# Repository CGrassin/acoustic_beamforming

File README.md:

# Acoustic Beamforming experiments

This repository contains all the ressources for my acoustic beamforming experiment using Arduino. This original article is here: http://charleslabs.fr/en/project-Acoustic+beamsteering+with+a+speaker+array

Various pieces of code/ressource are sorted by folder.

## Code_Pattern

This folder contains code to compute beamforming patterns.

The main script is beamforming_pattern_gen.py. Usage: `python3 beamforming_pattern_gen.py -h` (shows the help and options)

Sample output (`python3 beamforming_pattern_gen.py -f 1000 -a 10`):

Also included is a geogebra file for uniform amplitude law pattern simulation.

## Code_Arduino

This folder contains the code generator and the libraries to program the Arduino. It computes the timing to get the proper frequncy and phase between the elements. Usage:

```sh
python3 beamforming_code_gen.py -f 1000 -a 10
```

Output: Arduino code for the generation of a 1000Hz frequency wave, steered to +10 degrees.

Note: there is also a fully working, but deprecated Java version of this script that I created prior to the python version.

## Electronics

This folder contains the 12 channels signal generator PCB based around the FM62429 chips and the Arduino Nano microcontroller board. I used the open-source EDA KiCad.

## Experiments_Data

*WORK IN PROGRESS* This folder contains the data collected for each measurement, in CSV format. The first line of each CSV file contains all information to figure out it content.

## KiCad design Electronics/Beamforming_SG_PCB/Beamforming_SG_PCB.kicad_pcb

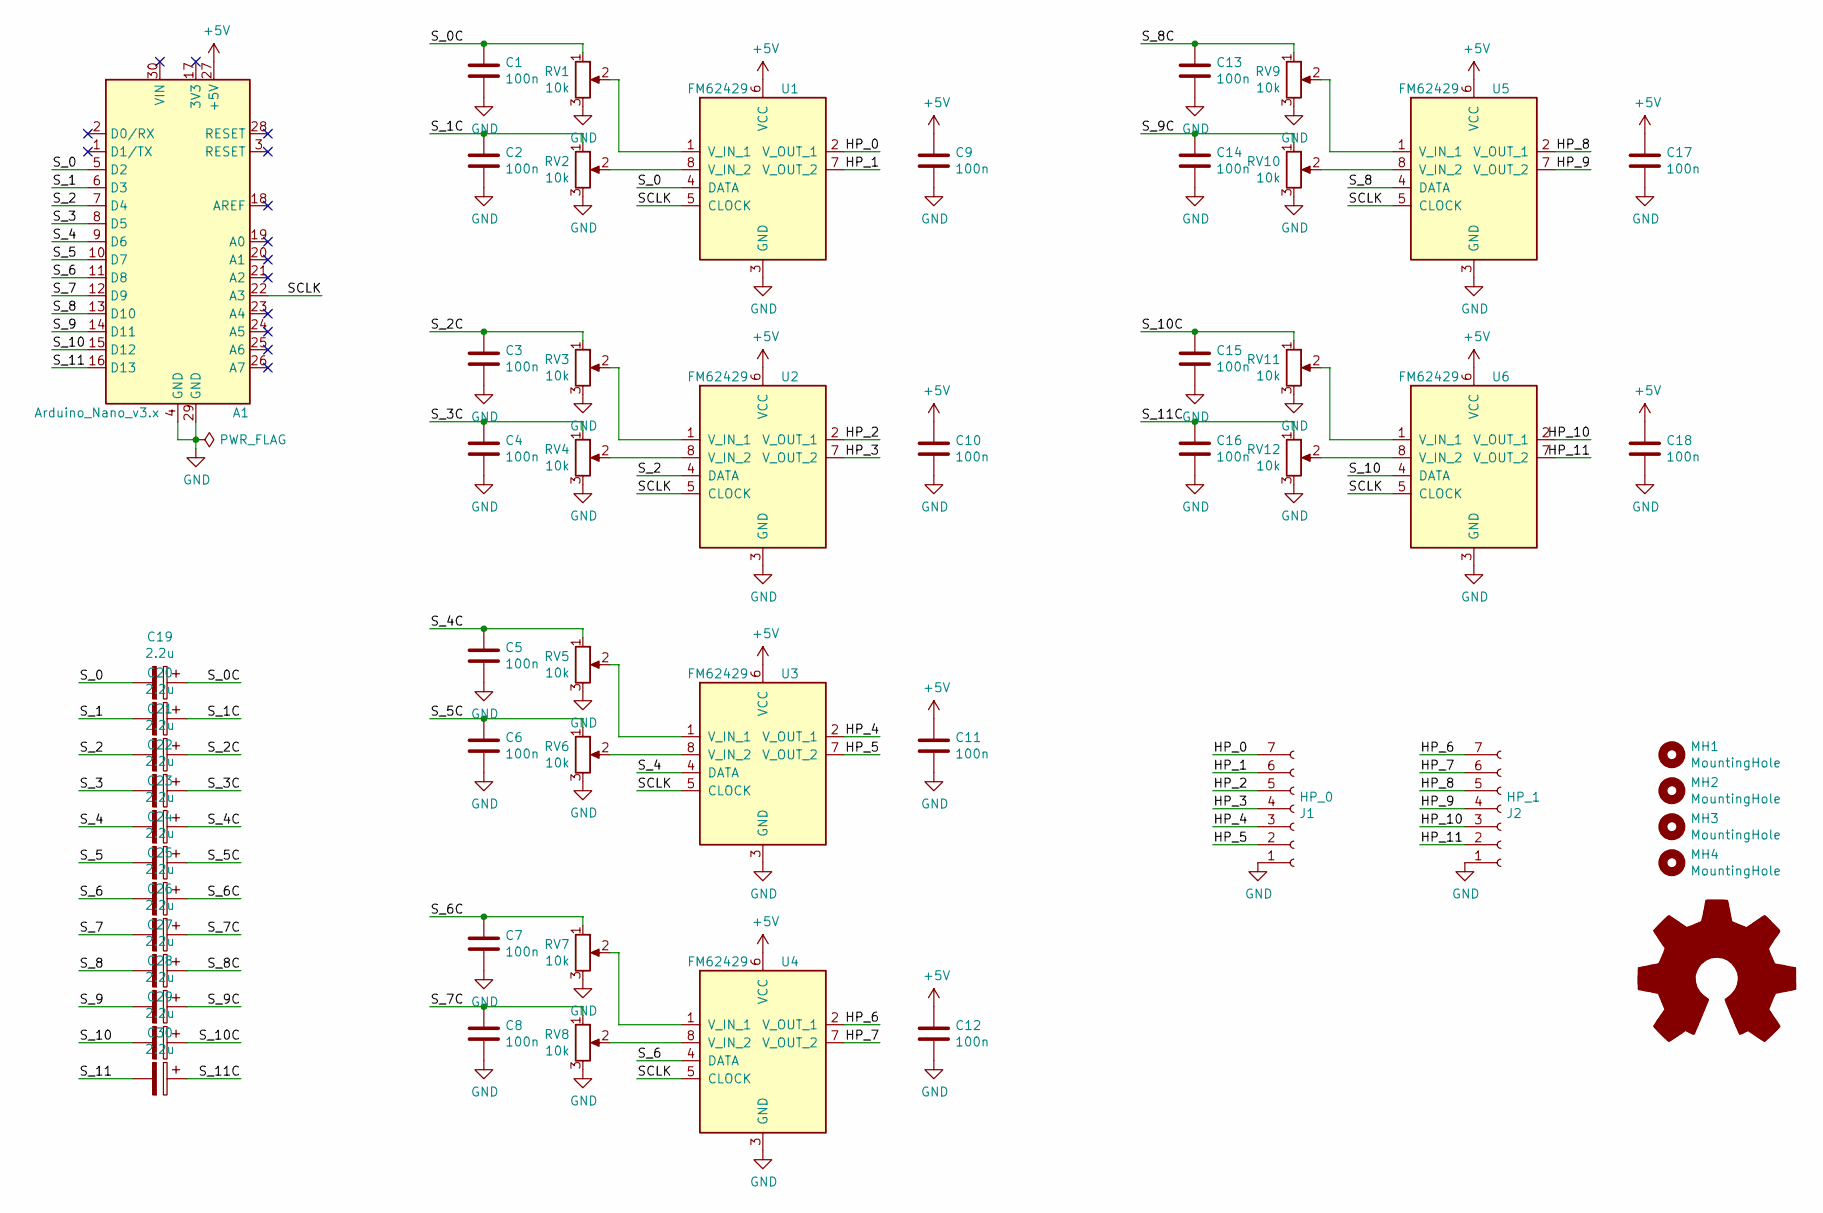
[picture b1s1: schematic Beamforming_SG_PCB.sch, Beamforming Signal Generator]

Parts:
A1: Arduino_Nano_v3.x; Arduino_Nano
C1, C2, C3, C4, C5, C6, C7, C8, C13, C14, C15, C16: 100n; C_0805_2012Metric
C9, C10, C11, C12, C17, C18: 100n; C_Disc_D4.3mm_W1.9mm_P5.00mm
C19, C20, C21, C22, C23, C24, C25, C26, C27, C28, C29, C30: 2.2u; C_0805_2012Metric
J1: HP_0; PinSocket_1x07_P2.54mm_Vertical
J2: HP_1; PinSocket_1x07_P2.54mm_Vertical
LOGO1: Logo_Open_Hardware_Large; OSHW-Symbol_8.9x8mm_SilkScreen
MH1, MH2, MH3, MH4: MountingHole; MountingHole_3.2mm_M3
RV1, RV2, RV3, RV4, RV5, RV6, RV7, RV8, RV9, RV10, RV11, RV12: 10k; Potentiometer_Bourns_3296W_Vertical
U1, U2, U3, U4, U5, U6: FM62429; DIP-8_W7.62mm

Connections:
+5V: A1.27 (+5V), C9.1, C10.1, C11.1, C12.1, C17.1, C18.1, U1.6 (VCC), U2.6 (VCC), U3.6 (VCC), U4.6 (VCC), U5.6 (VCC), U6.6 (VCC)
/HP_0: J1.7, U1.2 (V_OUT_1)
/HP_1: J1.6, U1.7 (V_OUT_2)
/HP_2: J1.5, U2.2 (V_OUT_1)
/HP_3: J1.4, U2.7 (V_OUT_2)
/HP_4: J1.3, U3.2 (V_OUT_1)
/HP_5: J1.2, U3.7 (V_OUT_2)
/HP_6: J2.7, U4.2 (V_OUT_1)
/HP_7: J2.6, U4.7 (V_OUT_2)
/HP_8: J2.5, U5.2 (V_OUT_1)
/HP_9: J2.4, U5.7 (V_OUT_2)
/HP_10: J2.3, U6.2 (V_OUT_1)
/HP_11: J2.2, U6.7 (V_OUT_2)
/SCLK: A1.22 (A3), U1.5 (CLOCK), U2.5 (CLOCK), U3.5 (CLOCK), U4.5 (CLOCK), U5.5 (CLOCK), U6.5 (CLOCK)
/S_0: A1.5 (D2), C19.2, U1.4 (DATA)
/S_0C: C1.1, C19.1, RV1.1
/S_1: A1.6 (D3), C20.2
/S_1C: C2.1, C20.1, RV2.1
/S_2: A1.7 (D4), C21.2, U2.4 (DATA)
/S_2C: C3.1, C21.1, RV3.1
/S_3: A1.8 (D5), C22.2
/S_3C: C4.1, C22.1, RV4.1
/S_4: A1.9 (D6), C23.2, U3.4 (DATA)
/S_4C: C5.1, C23.1, RV5.1
/S_5: A1.10 (D7), C24.2
/S_5C: C6.1, C24.1, RV6.1
/S_6: A1.11 (D8), C25.2, U4.4 (DATA)
/S_6C: C7.1, C25.1, RV7.1
/S_7: A1.12 (D9), C26.2
/S_7C: C8.1, C26.1, RV8.1
/S_8: A1.13 (D10), C27.2, U5.4 (DATA)
/S_8C: C13.1, C27.1, RV9.1
/S_9: A1.14 (D11), C28.2
/S_9C: C14.1, C28.1, RV10.1
/S_10: A1.15 (D12), C29.2, U6.4 (DATA)
/S_10C: C15.1, C29.1, RV11.1
/S_11: A1.16 (D13), C30.2
/S_11C: C16.1, C30.1, RV12.1
GND: A1.4 (GND), A1.29 (GND), C1.2, C2.2, C3.2, C4.2, C5.2, C6.2, C7.2, C8.2, C9.2, C10.2, C11.2, C12.2, C13.2, C14.2, C15.2, C16.2, C17.2, C18.2, J1.1, J2.1, RV1.3, RV2.3, RV3.3, RV4.3, RV5.3, RV6.3, RV7.3, RV8.3, RV9.3, RV10.3, RV11.3, RV12.3, U1.3 (GND), U2.3 (GND), U3.3 (GND), U4.3 (GND), U5.3 (GND), U6.3 (GND)
unnamed: RV1.2, U1.1 (V_IN_1)
unnamed: RV2.2, U1.8 (V_IN_2)
unnamed: RV3.2, U2.1 (V_IN_1)
unnamed: RV4.2, U2.8 (V_IN_2)
unnamed: RV5.2, U3.1 (V_IN_1)
unnamed: RV6.2, U3.8 (V_IN_2)
unnamed: RV7.2, U4.1 (V_IN_1)
unnamed: RV8.2, U4.8 (V_IN_2)
unnamed: RV9.2, U5.1 (V_IN_1)
unnamed: RV10.2, U5.8 (V_IN_2)
unnamed: RV11.2, U6.1 (V_IN_1)
unnamed: RV12.2, U6.8 (V_IN_2)

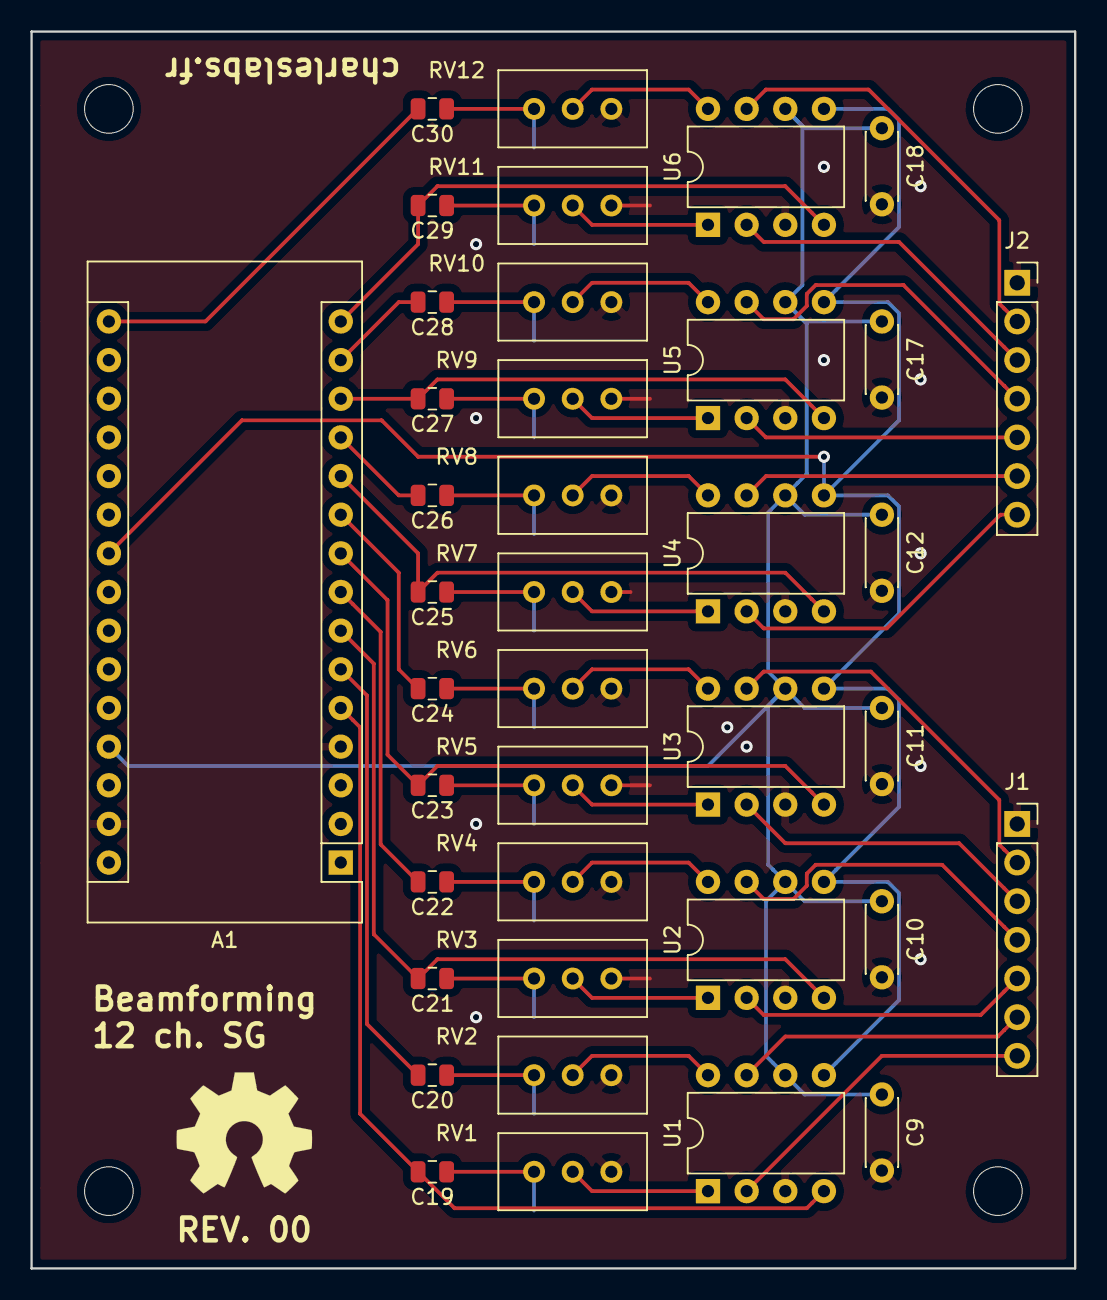
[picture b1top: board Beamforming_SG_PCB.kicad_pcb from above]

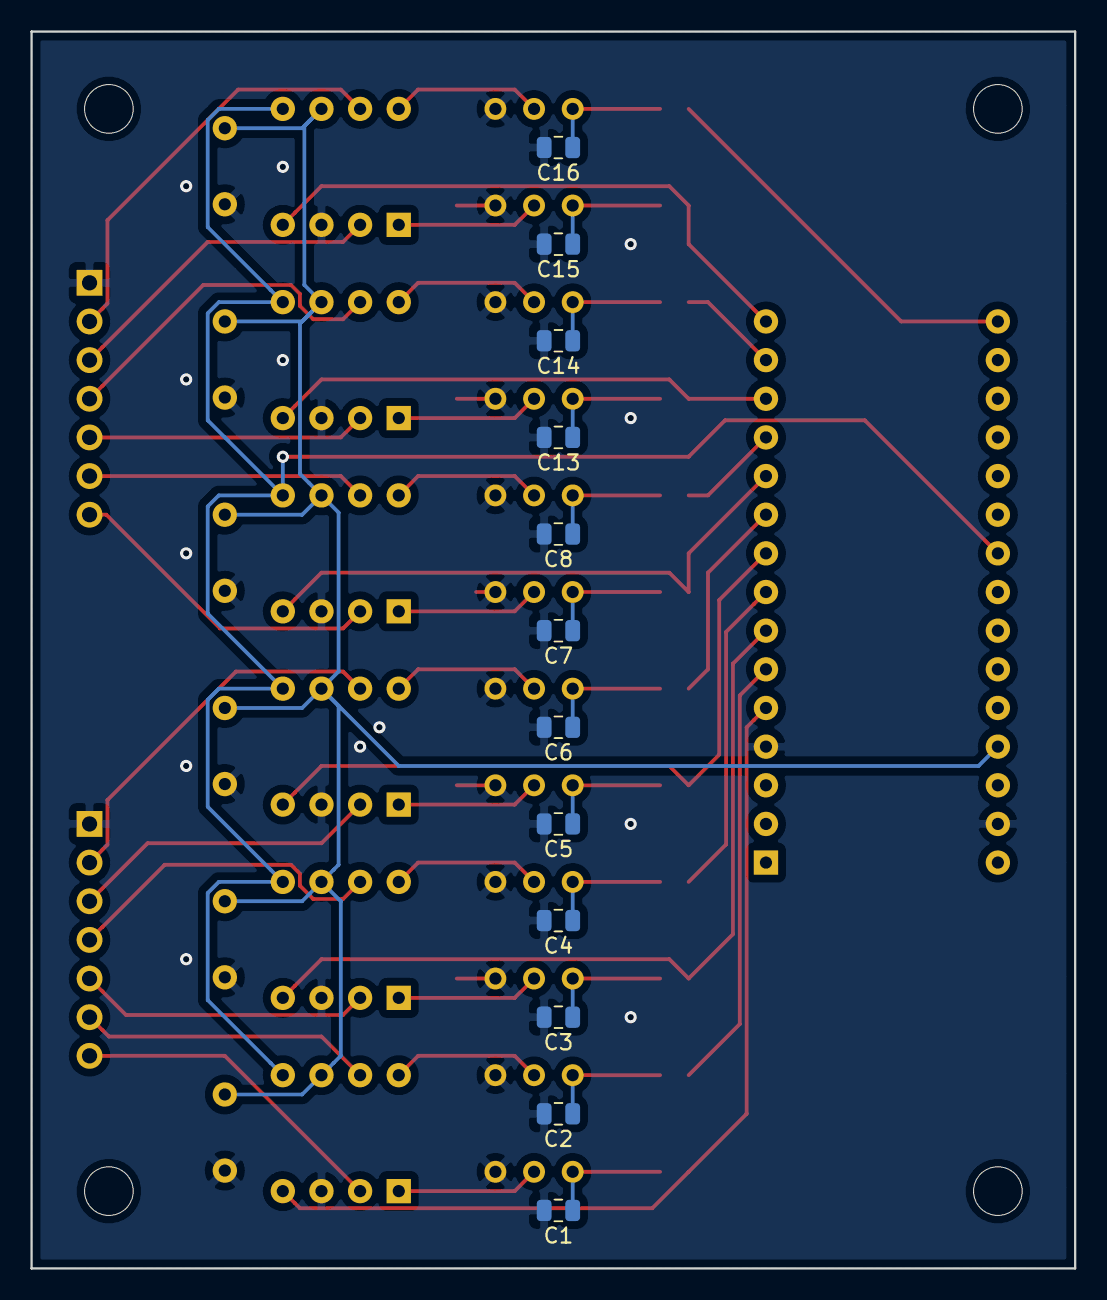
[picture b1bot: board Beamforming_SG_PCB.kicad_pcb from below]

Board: 2 copper layers, 68.6 x 81.3 mm, 56 parts (12 on the bottom side), 51 nets.

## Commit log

2020-03-08 Fixed bug in code generation
2020-03-09 Fixed display in pattern gen & nf distance in code gen
2020-03-15 Major update for publication
2023-02-22 Fix issue #1
